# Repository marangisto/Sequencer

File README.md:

# Sequencer
Modular sequence control unit

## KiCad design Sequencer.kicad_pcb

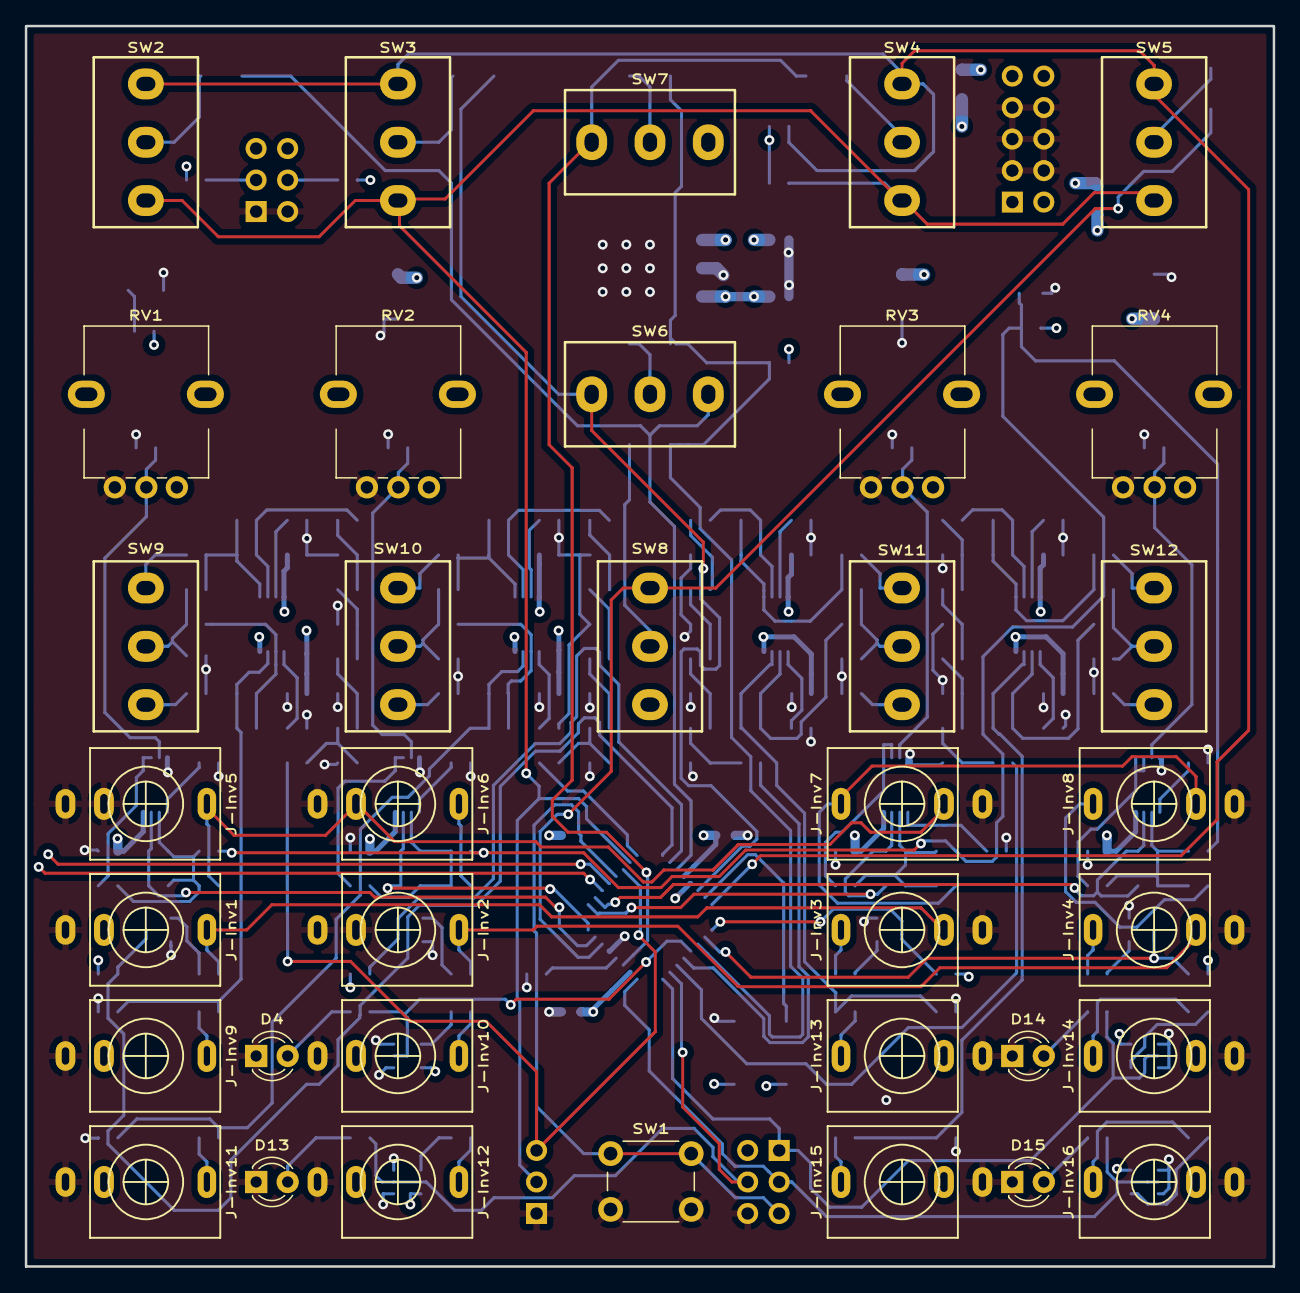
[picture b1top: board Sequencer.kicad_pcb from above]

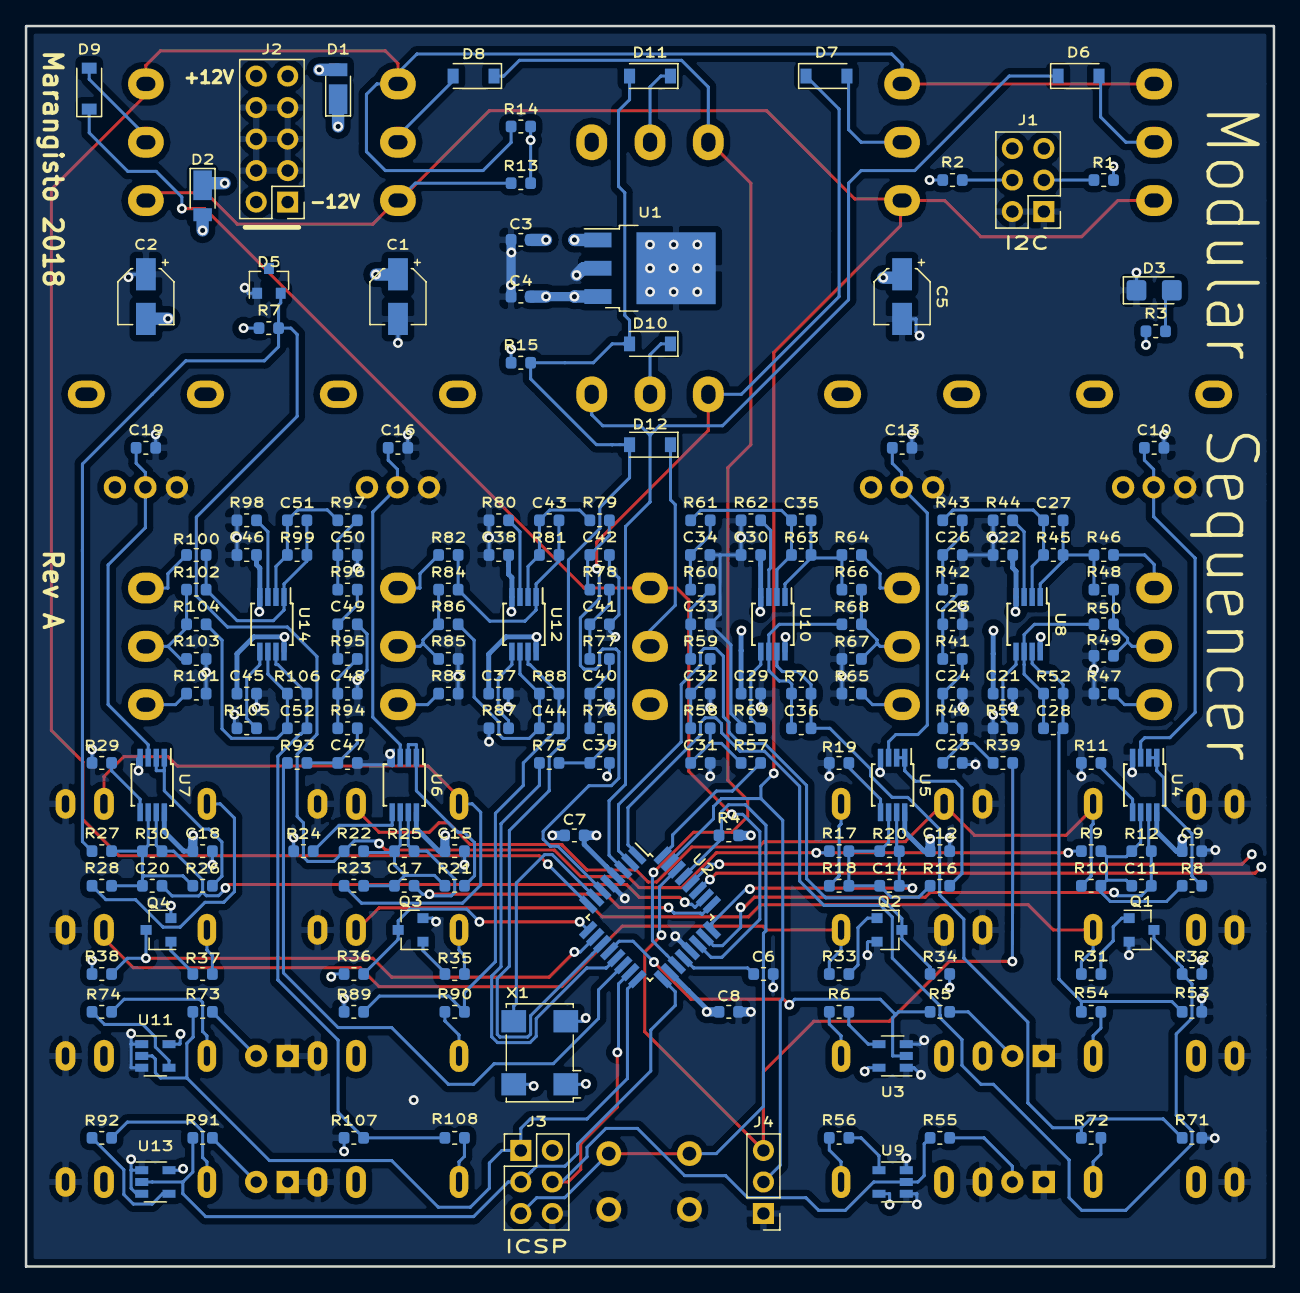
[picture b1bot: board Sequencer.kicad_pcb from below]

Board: 4 copper layers, 100.6 x 100.0 mm, 230 parts (194 on the bottom side), 139 nets.

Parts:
C1, C2, C5: 10u; CP_Elec_4x5.8
C3, C4, C6, C7, C8, C9, C10, C12, C13, C15, C16, C18, C19, C21, C22, C29, C30, C37, C38, C45, C46: 100n; C_0603_1608Metric
C11, C14, C17, C20: 470p; C_0603_1608Metric
C23, C24, C25, C26, C31, C32, C33, C34, C39, C40, C41, C42, C47, C48, C49, C50: 47n; C_0603_1608Metric
C27, C28, C35, C36, C43, C44, C51, C52: 100p; C_0603_1608Metric
D1, D2: DFLR1400-7; D_PowerDI-123
D3: LED; LED_1206_3216Metric_Castellated
D4, D13, D14, D15: LED; LED_D3.0mm
D5: LM4040DBZ-10; SOT-23
D6, D7, D8, D9, D10, D11, D12: 1N4148; D_SOD-123
J1, J3: Conn_02x03_Odd_Even; PinHeader_2x03_P2.54mm_Vertical
J2: Conn_02x05_Odd_Even; PinHeader_2x05_P2.54mm_Vertical
J4: Conn_01x03; PinHeader_1x03_P2.54mm_Vertical
J-Inv1, J-Inv2, J-Inv3, J-Inv4, J-Inv5, J-Inv6, J-Inv7, J-Inv8, J-Inv9, J-Inv10, J-Inv11, J-Inv12, J-Inv13, J-Inv14, J-Inv15, J-Inv16: AudioJack2_Ground_Switch; PJ398SM
Q1, Q2, Q3, Q4: BC847; SOT-23
R1, R2: 4k7; R_0603_1608Metric
R3, R5, R55, R73, R91: 330; R_0603_1608Metric
R4, R13, R14, R15, R32, R34, R36, R38: 10k; R_0603_1608Metric
R6, R54, R56, R72, R74, R90, R92, R108: 1k; R_0603_1608Metric
R7, R48, R49, R66, R67, R84, R85, R102, R103: 2k2; R_0603_1608Metric
R8, R10, R12, R16, R18, R20, R21, R23, R25, R26, R28, R30, R31, R33, R35, R37, R53, R71, R89, R107: 100k; R_0603_1608Metric
R9, R17, R22, R27: 200k; R_0603_1608Metric
R11, R19, R24, R29: 47k; R_0603_1608Metric
R39, R40, R41, R42, R46, R57, R58, R59, R60, R64, R75, R76, R77, R78, R82, R93, R94, R95, R96, R100: 470; R_0603_1608Metric
R43, R45, R50, R52, R61, R63, R68, R70, R79, R81, R86, R88, R97, R99, R104, R106: 68k; R_0603_1608Metric
R44, R51, R62, R69, R80, R87, R98, R105: 33k; R_0603_1608Metric
R47, R65, R83, R101: 1k5; R_0603_1608Metric
RV1, RV2, RV3, RV4: 100k; AlpsRK09K
SW1: SW_Push; SW_PUSH_6mm_H9.5mm
SW2, SW3, SW4, SW5, SW6, SW9, SW10, SW11, SW12: SW_SPDT_MSM; SPDT
SW7, SW8: SW_SPDT; SPDT
U1: L7805; TO-252-3_TabPin2
U2: ATmega328PB-AU; TQFP-32_7x7mm_P0.8mm
U3, U9, U11, U13: 74AHCT1G125; SOT-23-5
U4, U5, U6, U7: MCP6002-xMS; MSOP-8_3x3mm_P0.65mm
U8, U10, U12, U14: TL072; MSOP-8_3x3mm_P0.65mm
X1: 20MHz; Oscillator_SMD_IQD_IQXO70-4Pin_7.5x5.0mm

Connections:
+5V: C4.1, C5.1, C7.1, C8.2, C9.1, C12.1, C15.1, C18.1, J1.5, J1.6, J3.2, J-Inv1.TN, R1.1, R2.1, R3.1, R4.1, R13.1, R14.1, R15.1, R32.1, R34.1, R36.1, R38.1, RV1.1, RV2.1, RV3.1, RV4.1, U1.3, U2.4, U2.18, U3.5, U4.8, U5.8, U6.8, U7.8, U9.5, U11.5, U13.5, X1.1, X1.4
+12V: C1.1, C3.1, C21.1, C29.1, C37.1, C45.1, D1.1, U1.1, U8.8, U10.8, U12.8, U14.8
-12V: C2.2, C22.2, C30.2, C38.2, C46.2, D2.2, R7.1, U8.4, U10.4, U12.4, U14.4
/CVIn/In: J-Inv5.T, J-Inv6.TN, J-Inv7.TN, R10.1
/CVOut/Out: J-Inv9.T, R54.1
/DigitalIn/In: J-Inv1.T, J-Inv3.TN, R31.1
/DigitalOut/Out: J-Inv10.T, R6.1
/sheet5C14AC01/In: J-Inv6.T, R18.1
/sheet5C25BE7D/Out: J-Inv13.T, R90.1
/sheet5C25BE68/Out: J-Inv14.T, R74.1
/sheet5C25BE94/Out: J-Inv16.T, R92.1
/sheet5C25BEB7/Out: J-Inv15.T, R108.1
/sheet5C230BAE/Out: J-Inv12.T, R56.1
/sheet5C230BC3/Out: J-Inv11.T, R72.1
/sheet5C1536C4/In: J-Inv7.T, J-Inv8.TN, R23.1
/sheet5C1536DC/In: J-Inv8.T, R28.1
/sheet5C19208D/In: J-Inv4.T, R37.1
/sheet5C188821/In: J-Inv2.T, J-Inv4.TN, R33.1
/sheet5C192077/In: J-Inv3.T, R35.1
CLK0: Q1.3, R32.2, U2.1
CLK1: Q3.3, R36.2, U2.9
CV0: J4.3, R39.2, U2.30
CV1: R57.2, U2.32
CV2: R75.2, U2.13
CV3: R93.2, U2.14
END0: C14.1, R20.1, U2.24, U5.7
END1: C20.1, R30.1, U2.26, U7.7
GND: C1.2, C2.1, C3.2, C4.2, C5.2, C6.1, C7.2, C8.1, C9.2, C10.2, C12.2, C13.2, C15.2, C16.2, C18.2, C19.2, C21.2, C22.1, C23.2, C24.2, C25.2, C26.2, C29.2, C30.1, C31.2, C32.2, C33.2, C34.2, C37.2, C38.1, C39.2, C40.2, C41.2, C42.2, C45.2, C46.1, C47.2, C48.2, C49.2, C50.2, D3.1, D4.1, D5.1, D13.1, D14.1, D15.1, J1.1, J1.2, J2.3, J2.4, J2.5, J2.6, J2.7, J2.8, J3.6, J4.1, J-Inv1.S, J-Inv2.S, J-Inv2.TN, J-Inv3.S, J-Inv4.S, J-Inv5.S, J-Inv5.TN, J-Inv6.S, J-Inv7.S, J-Inv8.S, J-Inv9.S, J-Inv10.S, J-Inv11.S, J-Inv12.S, J-Inv13.S, J-Inv14.S, J-Inv15.S, J-Inv16.S, Q1.2, Q2.2, Q3.2, Q4.2, R11.2, R19.2, R24.2, R29.2, R44.1, R47.2, R49.2, R51.1, R53.2, R62.1, R65.2, R67.2, R69.1, R71.2, R80.1, R83.2, R85.2, R87.1, R89.2, R98.1, R101.2, R103.2, R105.1, R107.2, RV1.3, RV2.3, RV3.3, RV4.3, SW1.2, U1.2, U2.5, U2.21, U3.1, U3.3, U4.4, U5.4, U6.4, U7.4, U9.1, U9.3, U11.1, U11.3, U13.1, U13.3, X1.2
unnamed: C6.2, U2.20
unnamed: C10.1, RV1.2, U4.3
unnamed: C11.2, R8.2, R9.2, R10.2, R12.2, U4.6
unnamed: C13.1, RV2.2, U5.3
unnamed: C14.2, R16.2, R17.2, R18.2, R20.2, U5.6
unnamed: C16.1, RV3.2, U6.3
unnamed: C17.2, R21.2, R22.2, R23.2, R25.2, U6.6
unnamed: C19.1, RV4.2, U7.3
unnamed: C20.2, R26.2, R27.2, R28.2, R30.2, U7.6
unnamed: C23.1, R39.1, R40.2
unnamed: C24.1, R40.1, R41.2
unnamed: C25.1, R41.1, R42.2
unnamed: C26.1, R42.1, R43.2
unnamed: C27.1, R45.1, R46.1, R48.1, U8.1
unnamed: C27.2, R43.1, R45.2, U8.2
unnamed: C28.1, R52.1, R53.1, R54.2, U8.7
unnamed: C28.2, R50.2, R52.2, U8.6
unnamed: C31.1, R57.1, R58.2
unnamed: C32.1, R58.1, R59.2
unnamed: C33.1, R59.1, R60.2
unnamed: C34.1, R60.1, R61.2
unnamed: C35.1, R63.1, R64.1, R66.1, U10.1
unnamed: C35.2, R61.1, R63.2, U10.2
unnamed: C36.1, R70.1, R71.1, R72.2, U10.7
unnamed: C36.2, R68.2, R70.2, U10.6
unnamed: C39.1, R75.1, R76.2
unnamed: C40.1, R76.1, R77.2
unnamed: C41.1, R77.1, R78.2
unnamed: C42.1, R78.1, R79.2
unnamed: C43.1, R81.1, R82.1, R84.1, U12.1
unnamed: C43.2, R79.1, R81.2, U12.2
unnamed: C44.1, R88.1, R89.1, R90.2, U12.7
unnamed: C44.2, R86.2, R88.2, U12.6
unnamed: C47.1, R93.1, R94.2
unnamed: C48.1, R94.1, R95.2
unnamed: C49.1, R95.1, R96.2
unnamed: C50.1, R96.1, R97.2
unnamed: C51.1, R99.1, R100.1, R102.1, U14.1
unnamed: C51.2, R97.1, R99.2, U14.2
unnamed: C52.1, R106.1, R107.1, R108.2, U14.7
unnamed: C52.2, R104.2, R106.2, U14.6
unnamed: D1.2, J2.9, J2.10
unnamed: D2.1, J2.1, J2.2
unnamed: D3.2, R3.2
unnamed: D4.2, R5.2
unnamed: D6.2, SW2.2
unnamed: D7.2, SW3.2
unnamed: D8.2, SW4.2
unnamed: D9.2, SW5.2
unnamed: D10.1, SW6.2
unnamed: D11.1, SW7.2
unnamed: D12.1, SW8.2
unnamed: D13.2, R55.2
unnamed: D14.2, R73.2
unnamed: D15.2, R91.2
unnamed: J3.5, R4.2, SW1.1, U2.29
unnamed: Q1.1, R31.2
unnamed: Q2.1, R33.2
unnamed: Q3.1, R35.2
unnamed: Q4.1, R37.2
unnamed: R6.2, U3.4
unnamed: R8.1, U4.1, U4.2
unnamed: R11.1, U4.5
unnamed: R16.1, U5.1, U5.2
unnamed: R19.1, U5.5
unnamed: R21.1, U6.1, U6.2
unnamed: R24.1, U6.5
unnamed: R26.1, U7.1, U7.2
unnamed: R29.1, U7.5
unnamed: R44.2, U8.3
unnamed: R46.2, SW9.3
unnamed: R47.1, SW9.1
unnamed: R48.2, R49.1, R50.1, SW9.2
unnamed: R51.2, U8.5
unnamed: R56.2, U9.4
unnamed: R62.2, U10.3
unnamed: R64.2, SW10.3
unnamed: R65.1, SW10.1
unnamed: R66.2, R67.1, R68.1, SW10.2
unnamed: R69.2, U10.5
unnamed: R74.2, U11.4
unnamed: R80.2, U12.3
unnamed: R82.2, SW11.3
unnamed: R83.1, SW11.1
unnamed: R84.2, R85.1, R86.1, SW11.2
unnamed: R87.2, U12.5
unnamed: R92.2, U13.4
unnamed: R98.2, U14.3
unnamed: R100.2, SW12.3
unnamed: R101.1, SW12.1
unnamed: R102.2, R103.1, R104.1, SW12.2
unnamed: R105.2, U14.5
unnamed: U2.7, X1.3
RST0: Q2.3, R34.2, U2.2
RST1: Q4.3, R38.2, U2.10
SCL: J1.4, R2.2, U2.28
SDA: J1.3, R1.2, U2.27
STA0: C11.1, R12.1, U2.23, U4.7
STA1: C17.1, R25.1, U2.25, U6.7
Scan0: D6.1, SW6.1, U2.3
Scan1: D7.1, SW6.3, U2.6
Scan2: D8.1, SW7.3, U2.19
Scan3: D9.1, SW8.3, U2.22
Sense0: J4.2, R13.2, SW2.1, SW3.1, SW4.1, SW5.1, U2.31
Sense1: R14.2, SW2.3, SW3.3, SW4.3, SW5.3, U2.8
Sense2: D10.2, D11.2, D12.2, R15.2, U2.11
TRIG0: R5.1, U2.12, U3.2
TRIG1: J3.4, R55.1, U2.15, U9.2
TRIG2: J3.1, R73.1, U2.16, U11.2
TRIG3: J3.3, R91.1, U2.17, U13.2
VRef-10: D5.2, R7.2, R9.1, R17.1, R22.1, R27.1

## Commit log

2018-12-01 DAC filter desgin in spice.
2018-12-01 Minor LP adjustments.
2018-12-01 Initial design.
2018-12-01 Four output channels with triggers.
2018-12-01 Verified digital input protection.
2018-12-01 Modularized output channels.
2018-12-02 Clocks, resets and separate triggers.
2018-12-02 Spice model for CV inputs.
2018-12-02 Added CV input for start and end positions.
2018-12-02 Fixed some footprints and models.
2018-12-03 Correct power to MCP6004.
2018-12-09 Added control switches.
2018-12-10 Split all op-amps to dual and externalized all jacks.
2018-12-12 Inital placement.
2018-12-16 More layout.
2018-12-20 Added DXF files.
2018-12-23 More detailed placement.
2018-12-23 Finished input ADC and digital IO placement.
2018-12-24 PWM filter placement.
2018-12-25 Minor placement adjustments.
2018-12-25 Power section placement.
2018-12-25 PWM pin swap.
2018-12-25 Handrouted power and I2C.
2018-12-26 Autorouted remaining traces.
2018-12-26 Corrected one single DRC (unconnected).
2018-12-26 Fixed clearances on front copper.
2018-12-26 Fixed clearances on power layer.
2018-12-26 Back copper clearances.
2018-12-26 Front silk-screen.
2018-12-26 Back silk-screen.
2018-12-26 Branding.
2018-12-26 Front ground-pour.
2018-12-26 Back ground-pour.
2018-12-26 Added Gerbers.
2018-12-26 Added rules file.
2018-12-26 Added some renderings.
2018-12-31 Keep-outs for jacks.
2018-12-31 Symbol rescue on upgrade to 5.02.
2018-12-31 Added BOM.
2019-01-02 Added more renderings.
2019-01-02 Added a four-layer rendering.
2019-01-04 Updated BOM materials.
2019-01-17 Added BOM screenshot.
2019-05-05 Moved firmare from AVR project.
